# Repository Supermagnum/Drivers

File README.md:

This shield fits Arduino Mega 2560.
Including the items in the BOM, you will need:
Shield Stacking Headers compatible with Arduino MEGA 2560 
Each set has 5x1*8p header, 1x1*10p header, 1x2*18p header, 1x2*3p header
Arduino Mega 2560 Rev3 
Suitable USB cable, soldering iron,suitable wires.

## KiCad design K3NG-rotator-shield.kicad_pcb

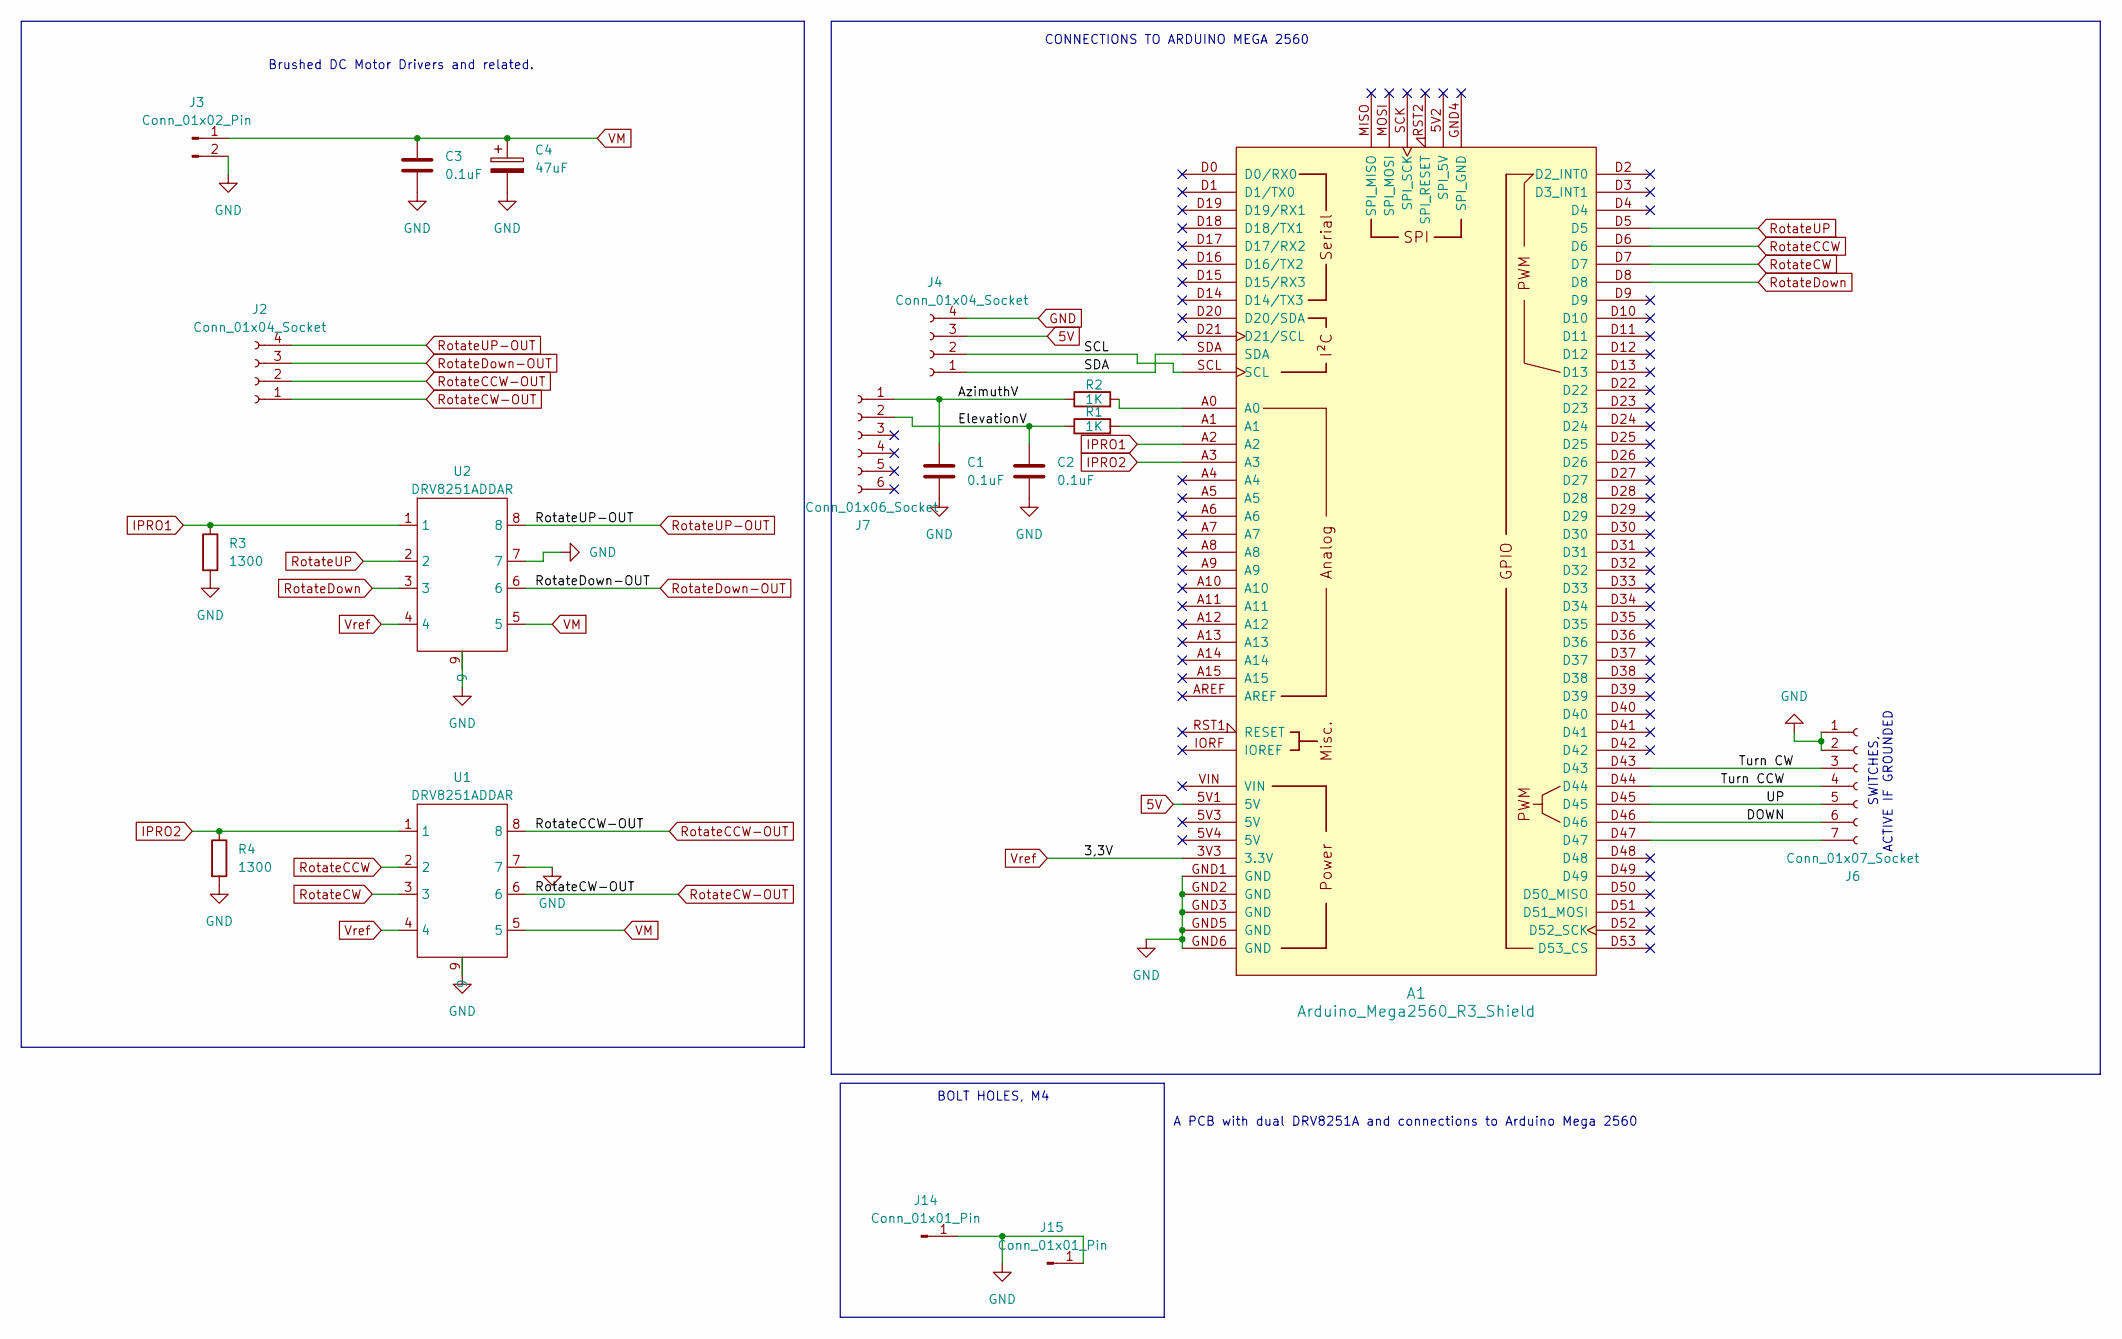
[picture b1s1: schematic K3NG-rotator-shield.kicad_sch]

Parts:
A1: Arduino_Mega2560_R3_Shield; Arduino_Mega2560_R3_K3NG
C1, C2, C3: 0.1uF; C_Disc_D4.7mm_W2.5mm_P5.00mm
C4: 47uF; CP_Radial_D10.0mm_P5.00mm
J2, J4: Conn_01x04_Socket; PinHeader_1x04_P2.54mm_Vertical
J3: Conn_01x02_Pin; SolderWire-1.5sqmm_1x02_P6mm_D1.7mm_OD3mm
J6: Conn_01x07_Socket; PinHeader_1x07_P2.54mm_Vertical
J7: Conn_01x06_Socket; PinHeader_1x06_P2.54mm_Vertical
J14, J15: Conn_01x01_Pin; MountingHole_4.3mm_M4_DIN965_Pad
R1, R2: 1K; R_Axial_DIN0204_L3.6mm_D1.6mm_P5.08mm_Horizontal
R3, R4: 1300; R_Axial_DIN0204_L3.6mm_D1.6mm_P5.08mm_Horizontal
U1, U2: DRV8251ADDAR; SOIC-8-1EP_3.9x4.9mm_P1.27mm_EP2.29x3mm_ThermalVias

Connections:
5V: A1.5V1 (5V), J4.3
/AzimuthV: C1.1, J7.1, R2.1
/DOWN: A1.D46, J6.6
/ElevationV: C2.1, J7.2, R1.1
/SCL: A1.SCL, J4.2
/SDA: A1.SDA, J4.1
/Turn CCW: A1.D44, J6.4
/Turn CW: A1.D43, J6.3
/UP: A1.D45, J6.5
GND: A1.GND1 (GND), A1.GND2 (GND), A1.GND3 (GND), A1.GND5 (GND), A1.GND6 (GND), C1.2, C2.2, C3.2, C4.2, J3.2, J4.4, J6.1, J6.2, J14.1, J15.1, R3.2, R4.2, U1.7, U1.9, U2.7, U2.9
IPRO1: A1.A2, R3.1, U2.1
IPRO2: A1.A3, R4.1, U1.1
unnamed: A1.A0, R2.2
unnamed: A1.A1, R1.2
unnamed: A1.D47, J6.7
RotateCCW: A1.D6, U1.2
RotateCCW-OUT: J2.2, U1.8
RotateCW: A1.D7, U1.3
RotateCW-OUT: J2.1, U1.6
RotateDown: A1.D8, U2.3
RotateDown-OUT: J2.3, U2.6
RotateUP: A1.D5, U2.2
RotateUP-OUT: J2.4, U2.8
VM: C3.1, C4.1, J3.1, U1.5, U2.5
Vref: A1.3V3 (3.3V), U1.4, U2.4

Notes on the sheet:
BOLT HOLES, M4
SWITCHES, ACTIVE IF GROUNDED
A PCB with dual DRV8251A and connections to Arduino Mega 2560
CONNECTIONS TO ARDUINO MEGA 2560
Brushed DC Motor Drivers and related.

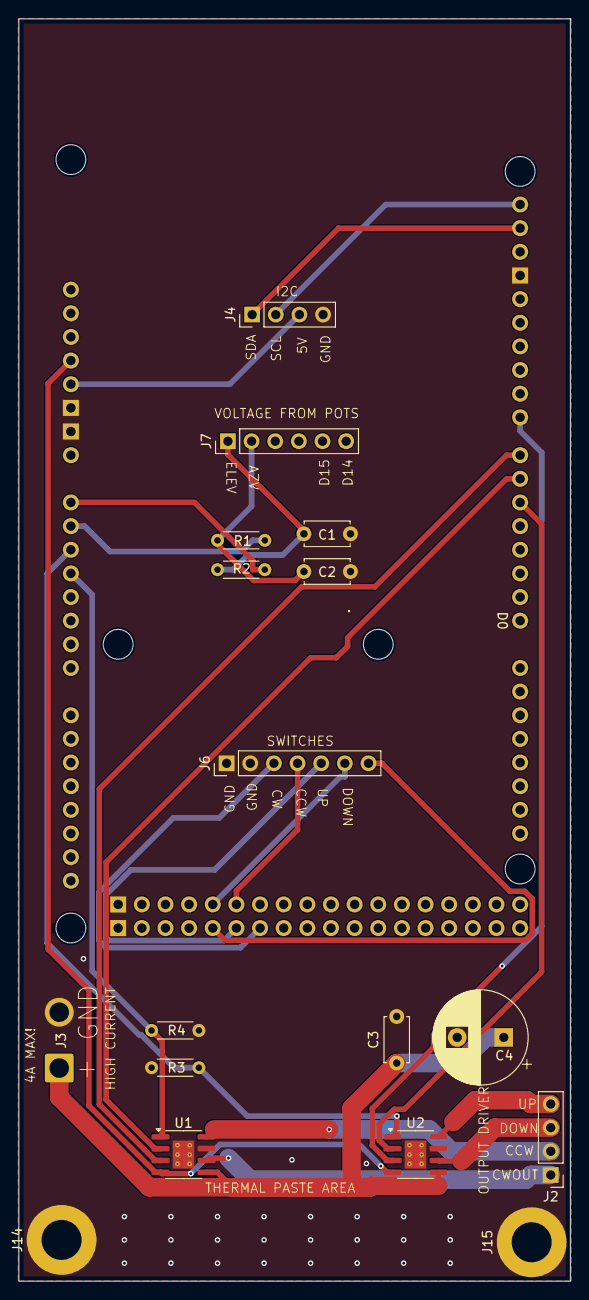
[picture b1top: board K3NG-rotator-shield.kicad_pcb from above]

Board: 2 copper layers, 59.2 x 135.6 mm, 18 parts (0 on the bottom side), 25 nets.

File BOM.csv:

"Reference","Value","Datasheet","Footprint","Qty","DNP","mfr"
"A1","Arduino_Mega2560_R3_Shield","https://docs.arduino.cc/hardware/mega-2560","sparkfun-electromech:Arduino_Mega2560_R3_K3NG","1","",""
"C1,C2,C3","0.1uF","~","Capacitor_THT:C_Disc_D4.7mm_W2.5mm_P5.00mm","3","","K104K10X7RF5UH5"
"C4","47uF","~","Capacitor_THT:CP_Radial_D10.0mm_P5.00mm","1","","  RNU1H470MDN1PH"
"J2,J4","Conn_01x04_Socket","~","Connector_PinHeader_2.54mm:PinHeader_1x04_P2.54mm_Vertical","2","","  1725672"
"J3","Conn_01x02_Pin","~","Connector_Wire:SolderWire-1.5sqmm_1x02_P6mm_D1.7mm_OD3mm","1","",""
"J6","Conn_01x07_Socket","~","Connector_PinHeader_2.54mm:PinHeader_1x07_P2.54mm_Vertical","1","","1725708"
"J7","Conn_01x06_Socket","~","Connector_PinHeader_2.54mm:PinHeader_1x06_P2.54mm_Vertical","1","","  1725698"
"J14,J15","Conn_01x01_Pin","~","MountingHole:MountingHole_4.3mm_M4_DIN965_Pad","2","",""
"R1,R2","1K","~","Resistor_THT:R_Axial_DIN0204_L3.6mm_D1.6mm_P5.08mm_Horizontal","2","","  YR1B1K0CC"
"R3,R4","1300","~","Resistor_THT:R_Axial_DIN0204_L3.6mm_D1.6mm_P5.08mm_Horizontal","2","","  MFR-25FBF52-1K3"
"U1,U2","DRV8251ADDAR","","Package_SO:SOIC-8-1EP_3.9x4.9mm_P1.27mm_EP2.29x3mm_ThermalVias","2","",""
